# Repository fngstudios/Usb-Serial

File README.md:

# Usb-Serial

MCP2200 based USB-Serial converter

## Features  
*FTDI/Arduino pinout  
*RTS auto-reset enables  
*3v3 / 5v selectable operating (supply and logic) voltage  
*Supply target switch  
*Drivers no needed    
*Female bottom connector  
*Micro usb connector  

## Images

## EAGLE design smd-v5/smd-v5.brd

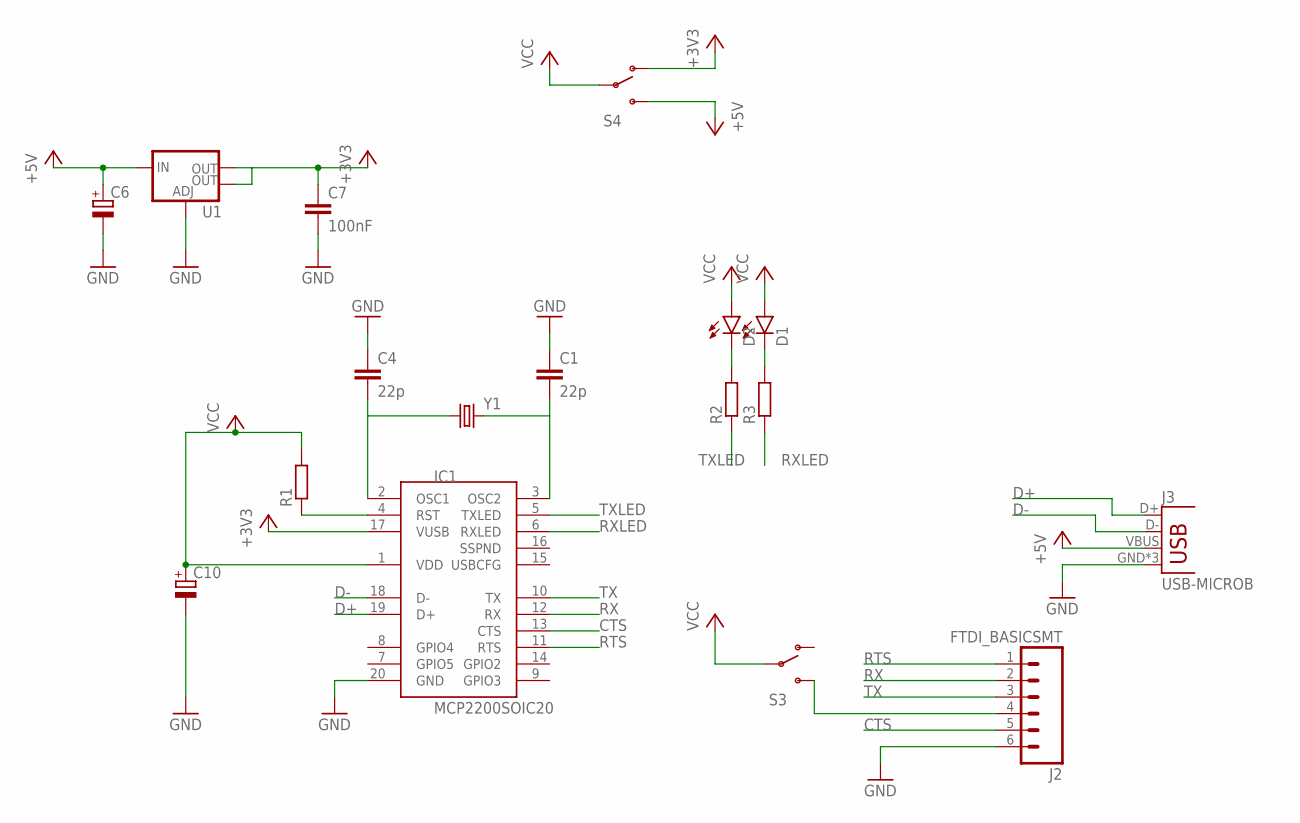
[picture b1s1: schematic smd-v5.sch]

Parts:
C1, C4: 22p; C1206K
C6, C10: CPOL-EUCT3528; CT3528
C7: 100nF; C1206K
D1, D2: LED1206; LED-1206
IC1: MCP2200SOIC20; SOIC20
J2: FTDI_BASICSMT; FTDI:DEVICE_RA_SMT_NOHOLES
J3: USB-MICROB
R1, R2, R3: R-EU_M1206; M1206
S3, S4: SWITCH-SPDT-SMD-A; SWITCH-SPST-SMD-A
U1: V_REG_LM1117SOT223; SOT223
Y1: CRYSTALSMD; HC49UP

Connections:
+3V3: C7.1, IC1.17 (VUSB), S4.1 (O), U1.2 (OUT), U1.4 (OUT)
+5V: C6.+, J3.VBUS, S4.3 (S), U1.3 (IN)
CTS: IC1.13 (CTS), J2.5
D+: IC1.19 (D+), J3.D+
D-: IC1.18 (D-), J3.D-
GND: C1.1, C4.1, C6.-, C7.2, C10.-, IC1.20 (GND), J2.6, J3.GND, J3.MT1 (GND), J3.MT2 (GND), U1.1 (ADJ)
unnamed: C4.2, IC1.2 (OSC1), Y1.1
unnamed: C1.2, IC1.3 (OSC2), Y1.2
unnamed: D2.C, R2.2
unnamed: D1.C, R3.2
unnamed: J2.4, S3.3 (S)
unnamed: IC1.4 (RST), R1.1
RTS: IC1.11 (RTS), J2.1
RX: IC1.12 (RX), J2.2
RXLED: IC1.6 (RXLED), R3.1
TX: IC1.10 (TX), J2.3
TXLED: IC1.5 (TXLED), R2.1
VCC: C10.+, D1.A, D2.A, IC1.1 (VDD), R1.2, S3.2, S4.2

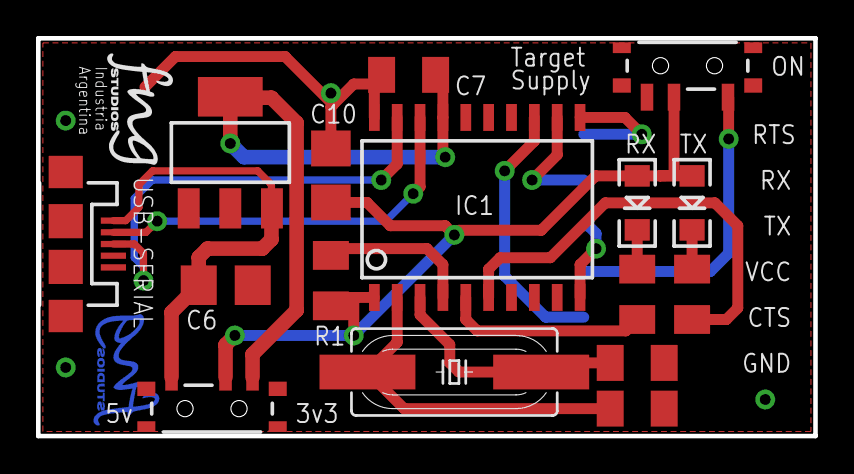
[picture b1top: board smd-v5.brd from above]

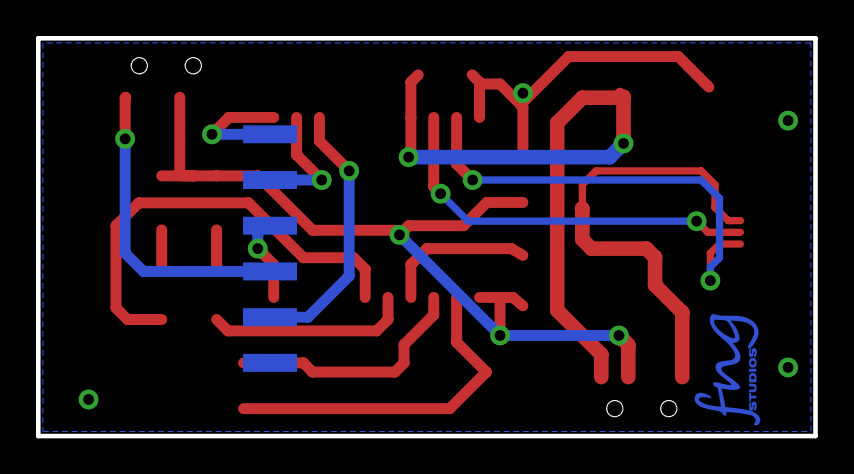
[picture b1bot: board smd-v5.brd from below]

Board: 2 copper layers, 43.2 x 22.1 mm, 19 parts (2 on the bottom side), 18 nets.

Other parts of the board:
U$1: LOGOFNGNAME0.5
U$2: LOGOFNG0.5

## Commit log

2016-12-18 Release

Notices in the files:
parts and their libraries:
SparkFun-PowerIC: Licensing: Creative Commons ShareAlike 4.0 International - https://creativecommons.org/licenses/by-sa/4.0
